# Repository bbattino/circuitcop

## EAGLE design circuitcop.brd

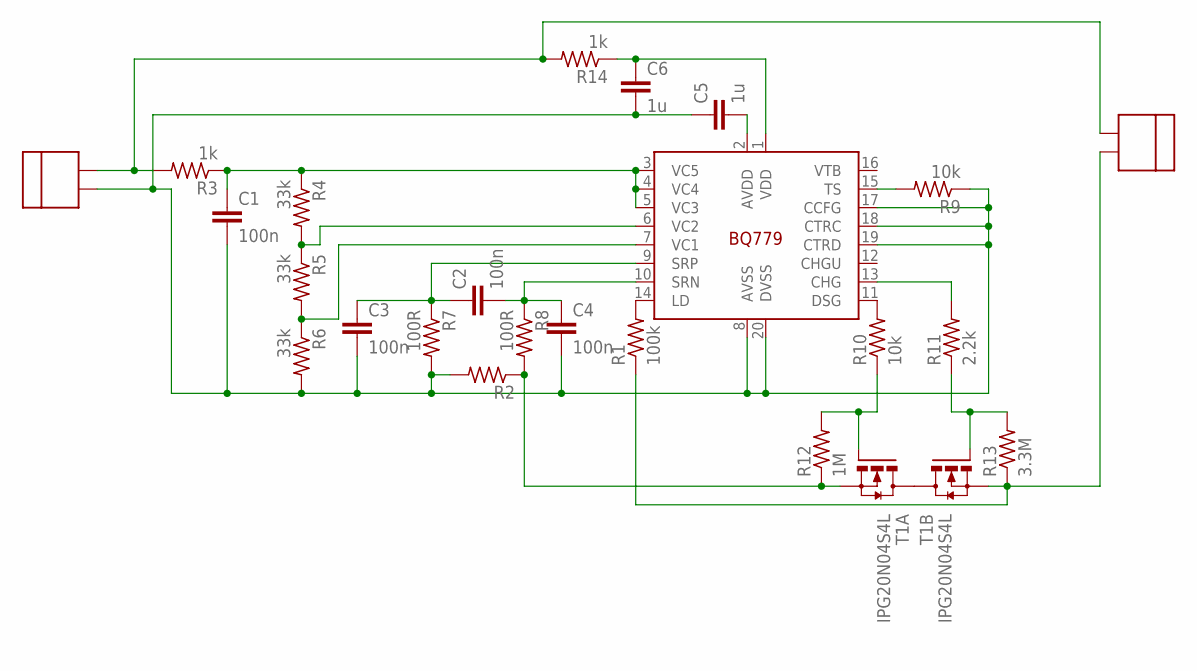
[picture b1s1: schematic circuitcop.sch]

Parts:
C1, C2, C3, C4: 100n; C0805
C5, C6: 1u; C0805
R1: 100k; R0805
R2: R-US_R1206; R1206
R3, R14: 1k; R0805
R4, R5, R6: 33k; R0805
R7, R8: 100R; R0805
R9, R10: 10k; R0805
R11: 2.2k; R0805
R12: 1M; R0805
R13: 3.3M; R0805
T1: IPG20N04S4L; PG-TDSON-8
U1: BQ779; TSSOP20
U$1, U$2: CTB5202/2

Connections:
GND: C1.2, C3.2, C4.2, C5.1, C6.2, R2.2, R6.2, R7.2, R9.1, U1.8 (AVSS), U1.17 (CCFG), U1.18 (CTRC), U1.19 (CTRD), U1.20 (DVSS), U$1.P$1 (1)
unnamed: R4.2, R5.1, U1.6 (VC2)
unnamed: R5.2, R6.1, U1.7 (VC1)
unnamed: C2.1, C3.1, R7.1, U1.9 (SRP)
unnamed: C2.2, C4.1, R8.1, U1.10 (SRN)
unnamed: C1.1, R3.1, R4.1, U1.3 (VC5), U1.4 (VC4), U1.5 (VC3)
unnamed: R2.1, R8.2, R12.1, T1.1 (S)
unnamed: R1.2, U1.14 (LD)
unnamed: R10.2, U1.11 (DSG)
unnamed: R9.2, U1.15 (TS)
unnamed: T1.5 (D), T1.6 (D), T1.7 (D), T1.8 (D), T1.TH1 (D), T1.TH2 (D)
unnamed: R10.1, R12.2, T1.2 (G)
unnamed: R11.2, U1.13 (CHG)
unnamed: R11.1, R13.2, T1.4 (G)
unnamed: C5.2, U1.2 (AVDD)
unnamed: R1.1, R13.1, T1.3 (S), U$2.P$2 (2)
unnamed: C6.1, R14.1, U1.1 (VDD)
VIN: R3.2, R14.2, U$1.P$2 (2), U$2.P$1 (1)

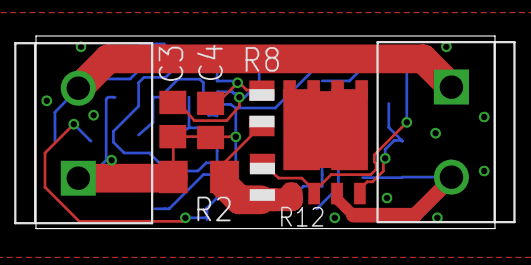
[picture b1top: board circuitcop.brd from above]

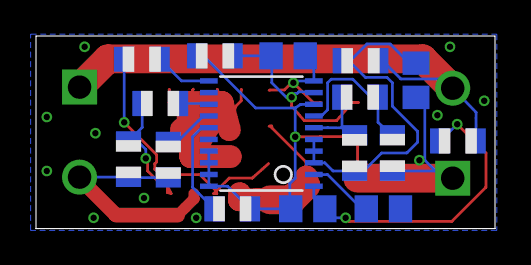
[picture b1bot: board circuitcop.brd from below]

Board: 2 copper layers, 25.5 x 10.7 mm, 24 parts (16 on the bottom side), 18 nets.

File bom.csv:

Qty;Qty to buy;Value;Device;Package;Parts;Description;Ref Farnell
1;;;R-US_R1206;R1206;R2;Shunt resistor;
2;0;100R;R-US_R0805;R0805;R7, R8;Resistor;N/A
1;0;100k;R-US_R0805;R0805;R1;Resistor;N/A
4;4;100n;C-EUC0805;C0805;C1, C2, C3, C4;Capacitor;
2;0;10k;R-US_R0805;R0805;R9, R10;Resistor;N/A
1;1;1M;R-US_R0805;R0805;R12;Resistor;
2;0;1k;R-US_R0805;R0805;R3, R14;Resistor;N/A
2;2;1u;C-EUC0805;C0805;C5, C6;Capacitor;
1;0;2.2k;R-US_R0805;R0805;R11;Resistor;N/A
1;1;3.3M;R-US_R0805;R0805;R13;Resistor;
3;0;33k;R-US_R0805;R0805;R4, R5, R6;Resistor;N/A
1;1;BQ779;BQ779;TSSOP20;U1;BQ77905;2617073
2;2;CTB5202/2;CTB5202/2;CTB5202/2;U$1, U$2;2 pins Terminal block;
1;1;IPG20N04S4L;IPG20N04S4L;PG-TDSON-8;T1;Dual N-channel MOSFET;2480842

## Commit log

2018-01-08 schematic and board first version
2018-01-09 worked on bom
2018-01-09 improved board
2018-01-09 removed DS store
